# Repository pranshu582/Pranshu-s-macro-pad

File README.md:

# Pranshu-s-macro-pad
Pranshu's submission for Hackpad

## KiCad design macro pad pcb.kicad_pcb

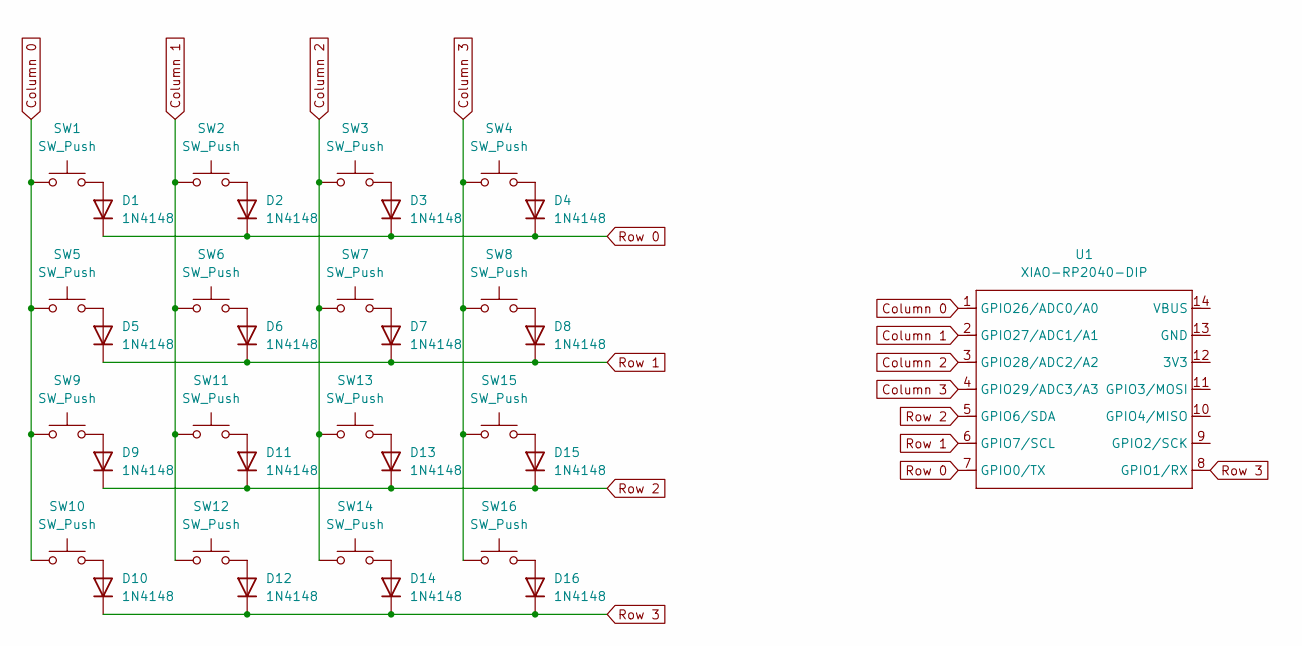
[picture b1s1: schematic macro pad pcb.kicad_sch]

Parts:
D1, D2, D3, D4, D5, D6, D7, D8, D9, D10, D11, D12, D13, D14, D15, D16: 1N4148; D_DO-35_SOD27_P7.62mm_Horizontal
SW1, SW2, SW3, SW4, SW5, SW6, SW7, SW8, SW9, SW10, SW11, SW12, SW13, SW14, SW15, SW16: SW_Push; SW_Cherry_MX_1.00u_PCB
U1: XIAO-RP2040-DIP

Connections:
Column 0: SW1.1, SW5.1, SW9.1, SW10.1, U1.1 (GPIO26/ADC0/A0)
Column 1: SW2.1, SW6.1, SW11.1, SW12.1, U1.2 (GPIO27/ADC1/A1)
Column 2: SW3.1, SW7.1, SW13.1, SW14.1, U1.3 (GPIO28/ADC2/A2)
Column 3: SW4.1, SW8.1, SW15.1, SW16.1, U1.4 (GPIO29/ADC3/A3)
unnamed: D1.2 (A), SW1.2
unnamed: D2.2 (A), SW2.2
unnamed: D3.2 (A), SW3.2
unnamed: D4.2 (A), SW4.2
unnamed: D5.2 (A), SW5.2
unnamed: D6.2 (A), SW6.2
unnamed: D7.2 (A), SW7.2
unnamed: D8.2 (A), SW8.2
unnamed: D9.2 (A), SW9.2
unnamed: D10.2 (A), SW10.2
unnamed: D11.2 (A), SW11.2
unnamed: D12.2 (A), SW12.2
unnamed: D13.2 (A), SW13.2
unnamed: D14.2 (A), SW14.2
unnamed: D15.2 (A), SW15.2
unnamed: D16.2 (A), SW16.2
Row 0: D1.1 (K), D2.1 (K), D3.1 (K), D4.1 (K), U1.7 (GPIO0/TX)
Row 1: D5.1 (K), D6.1 (K), D7.1 (K), D8.1 (K), U1.6 (GPIO7/SCL)
Row 2: D9.1 (K), D11.1 (K), D13.1 (K), D15.1 (K), U1.5 (GPIO6/SDA)
Row 3: D10.1 (K), D12.1 (K), D14.1 (K), D16.1 (K), U1.8 (GPIO1/RX)

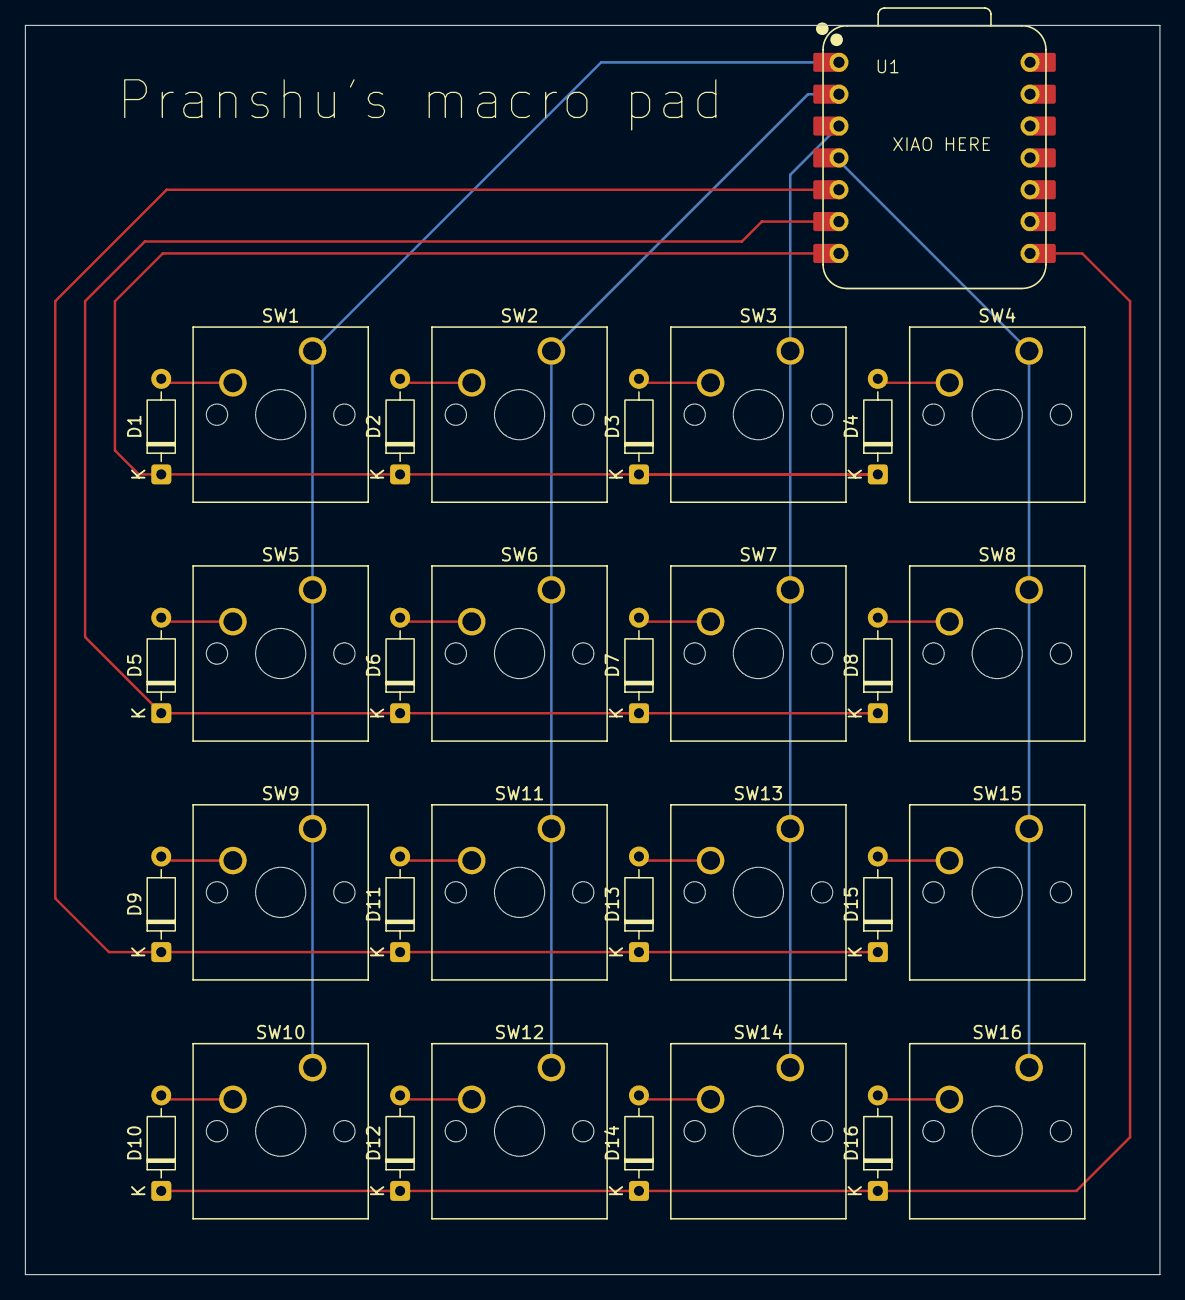
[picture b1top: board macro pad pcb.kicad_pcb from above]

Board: 2 copper layers, 90.5 x 99.6 mm, 33 parts (0 on the bottom side), 24 nets.

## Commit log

2025-11-30 Rename macro pad pcb.kicad_pro to PCB/macro pad pcb.kicad_pro
